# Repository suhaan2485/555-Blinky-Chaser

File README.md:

# 555-Blinky-Chaser
I made this through project a hack club stasis guide, this is an led chaser which blinks 10 LEDs in a variable speed sequence

Softwares used: KiCad, Google Chrome.

I have made a simple Blinky Chaser PCB which will repeat 10 LEDs light in a specific sequence using simple resistors, capacitors and the main NE555 Module,
You Can See the Live Demo Video Below or checout the "Live Demo.mp4" linked in this repo. 

# Schematics:

# PCB Layout:

# PCB 3D View:

# Bill Of Material:

| Reference | Qty | Value | DNP | Exclude from BOM | Exclude from Board | Footprint | Datasheet |
|----------|----------|----------|----------|----------|----------|----------|----------|
| C1 | 1 | 1μF |  |  |  | Capacitor_THT:CP_Radial_D5.0mm_P2.00mm |  |
| C2 | 1 | 0.01μF |  |  |  | Capacitor_THT:C_Disc_D7.5mm_W2.5mm_P5.00mm |  |
| D1,D2,D3,D4,D5,D6,D7,D8,D9,D10 | 10 | LED |  |  |  | LED_THT:LED_D3.0mm |  |
| J1 | 1 | Conn_01x02_Socket |  |  |  | Connector_PinHeader_2.54mm:PinHeader_1x02_P2.54mm_Vertical |  |
| J2 | 1 | Conn_01x01_Socket |  |  |  | Connector_PinHeader_2.54mm:PinHeader_1x02_P2.54mm_Vertical |  |
| J1 (+V) | 1 | 9V |  |  |  | Connector_PinHeader_2.54mm:PinHeader_1x02_P2.54mm_Vertical |  |
| R1 | 1 | 470 |  |  |  | Resistor_THT:R_Axial_DIN0207_L6.3mm_D2.5mm_P7.62mm_Horizontal |  |
| R3 | 1 | 1k |  |  |  | Resistor_THT:R_Axial_DIN0207_L6.3mm_D2.5mm_P7.62mm_Horizontal |  |
| RV2 | 1 | 50K |  |  |  | Potentiometer_THT:Potentiometer_Vishay_T93YA_Vertical |  |
| U1 | 1 | NE555P |  |  |  | Package_DIP:DIP-8_W7.62mm | http://www.ti.com/lit/ds/symlink/ne555.pdf |
| U2 | 1 | 4017 |  |  |  | Package_DIP:DIP-16_W7.62mm | http://www.intersil.com/content/dam/Intersil/documents/cd40/cd4017bms-22bms.pdf |

# Soldered Board:

# PCB Live Demo Video:
https://github.com/user-attachments/assets/2a811b2b-bb50-4437-af52-b02a34f7b085

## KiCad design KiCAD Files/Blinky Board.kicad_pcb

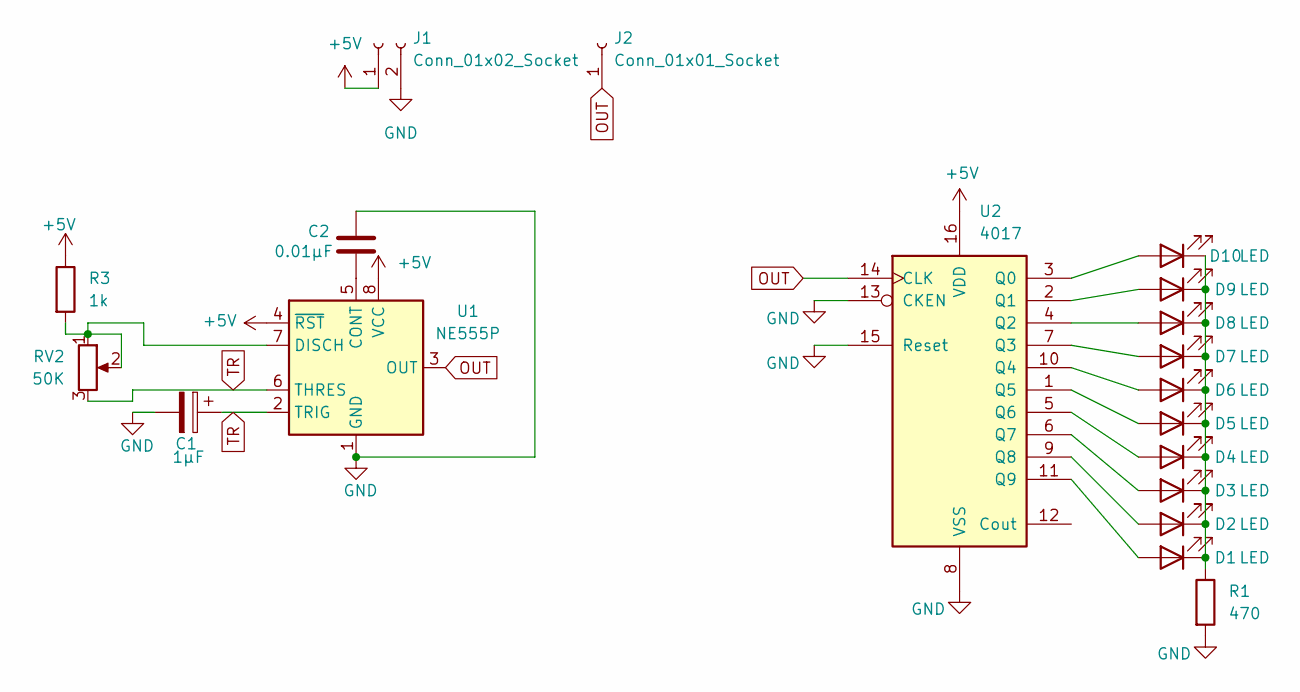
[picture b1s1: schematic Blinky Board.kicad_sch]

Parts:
C1: 1μF; CP_Radial_D5.0mm_P2.00mm
C2: 0.01μF; C_Disc_D7.5mm_W2.5mm_P5.00mm
D1, D2, D3, D4, D5, D6, D7, D8, D9, D10: LED; LED_D3.0mm
J1: Conn_01x02_Socket; PinHeader_1x02_P2.54mm_Vertical
J2: Conn_01x01_Socket; PinHeader_1x02_P2.54mm_Vertical
R1: 470; R_Axial_DIN0207_L6.3mm_D2.5mm_P7.62mm_Horizontal
R3: 1k; R_Axial_DIN0207_L6.3mm_D2.5mm_P7.62mm_Horizontal
RV2: 50K; Potentiometer_Vishay_T93YA_Vertical
U1: NE555P; DIP-8_W7.62mm
U2: 4017; DIP-16_W7.62mm

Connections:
+5V: J1.1, R3.1, U1.4 (~RST), U1.8 (VCC), U2.16 (VDD)
GND: C1.2, C2.1, J1.2, R1.2, U1.1 (GND), U2.8 (VSS), U2.13 (CKEN), U2.15 (Reset)
unnamed: D1.2 (A), U2.11 (Q9)
unnamed: D1.1 (K), D2.1 (K), D3.1 (K), D4.1 (K), D5.1 (K), D6.1 (K), D7.1 (K), D8.1 (K), D9.1 (K), D10.1 (K), R1.1
unnamed: D2.2 (A), U2.9 (Q8)
unnamed: D3.2 (A), U2.6 (Q7)
unnamed: D4.2 (A), U2.5 (Q6)
unnamed: D5.2 (A), U2.1 (Q5)
unnamed: D6.2 (A), U2.10 (Q4)
unnamed: D7.2 (A), U2.7 (Q3)
unnamed: D8.2 (A), U2.4 (Q2)
unnamed: D9.2 (A), U2.2 (Q1)
unnamed: D10.2 (A), U2.3 (Q0)
unnamed: C2.2, U1.5 (CONT)
unnamed: R3.2, RV2.1, RV2.2, U1.7 (DISCH)
OUT: J2.1 (Pin_1_1), U1.3 (OUT), U2.14 (CLK)
TR: C1.1, RV2.3, U1.2 (TRIG), U1.6 (THRES)

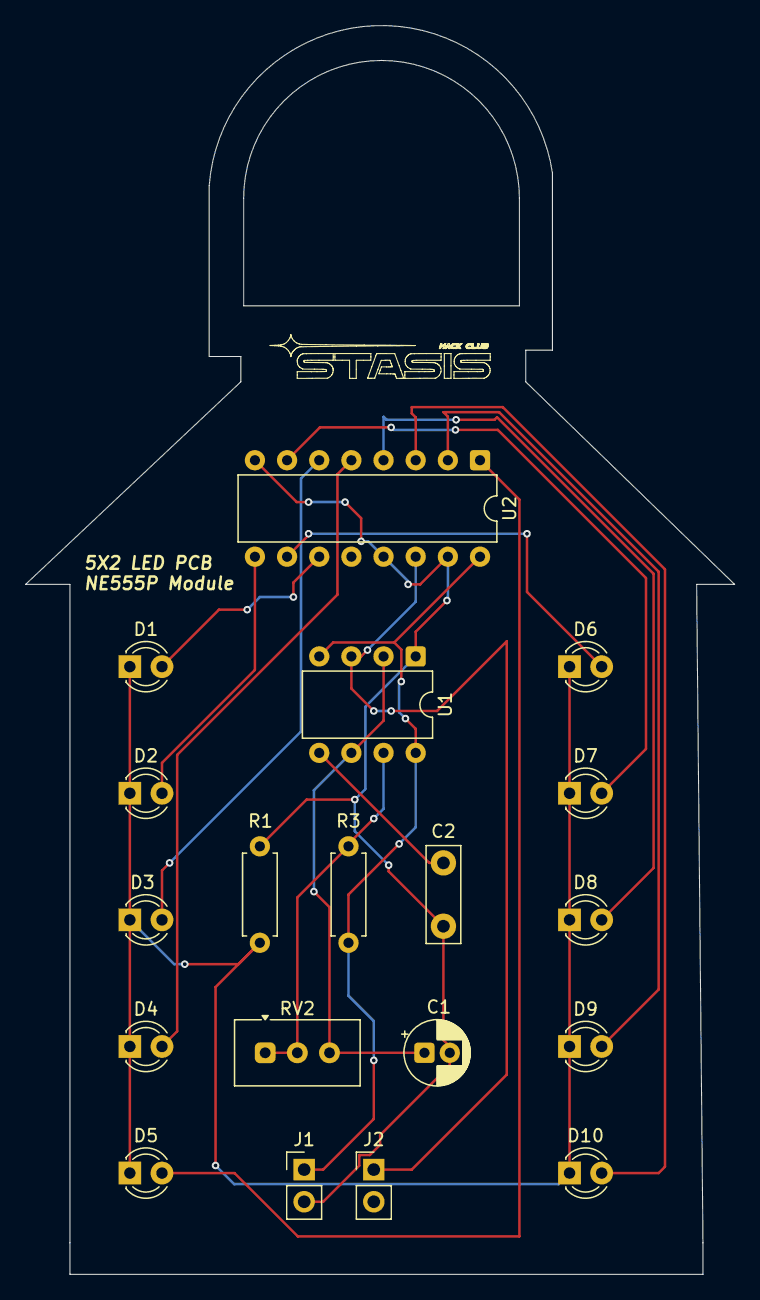
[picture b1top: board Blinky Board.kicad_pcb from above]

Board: 2 copper layers, 56.0 x 98.6 mm, 19 parts (0 on the bottom side), 17 nets.

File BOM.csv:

"Reference","Qty","Value","DNP","Exclude from BOM","Exclude from Board","Footprint","Datasheet"
"C1","1","1μF","","","","Capacitor_THT:CP_Radial_D5.0mm_P2.00mm",""
"C2","1","0.01μF","","","","Capacitor_THT:C_Disc_D7.5mm_W2.5mm_P5.00mm",""
"D1,D2,D3,D4,D5,D6,D7,D8,D9,D10","10","LED","","","","LED_THT:LED_D3.0mm",""
"J1","1","Conn_01x02_Socket","","","","Connector_PinHeader_2.54mm:PinHeader_1x02_P2.54mm_Vertical",""
"J2","1","Conn_01x01_Socket","","","","Connector_PinHeader_2.54mm:PinHeader_1x02_P2.54mm_Vertical",""
"R1","1","470","","","","Resistor_THT:R_Axial_DIN0207_L6.3mm_D2.5mm_P7.62mm_Horizontal",""
"R3","1","1k","","","","Resistor_THT:R_Axial_DIN0207_L6.3mm_D2.5mm_P7.62mm_Horizontal",""
"RV2","1","50K","","","","Potentiometer_THT:Potentiometer_Vishay_T93YA_Vertical",""
"U1","1","NE555P","","","","Package_DIP:DIP-8_W7.62mm","http://www.ti.com/lit/ds/symlink/ne555.pdf"
"U2","1","4017","","","","Package_DIP:DIP-16_W7.62mm","http://www.intersil.com/content/dam/Intersil/documents/cd40/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"

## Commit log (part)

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2026-04-23 PCB Board 3D View
    This was added for understanding how the board will look like once the pcb is finalised and to test test the layout in 3D.
2026-04-23 PCB, PRO and Schematics Files
    Have been added the base kicad
2026-04-23 Gerber Zip File
    An Gerber File has been uploaded so that it can be easily supplied to the pcb provider.
